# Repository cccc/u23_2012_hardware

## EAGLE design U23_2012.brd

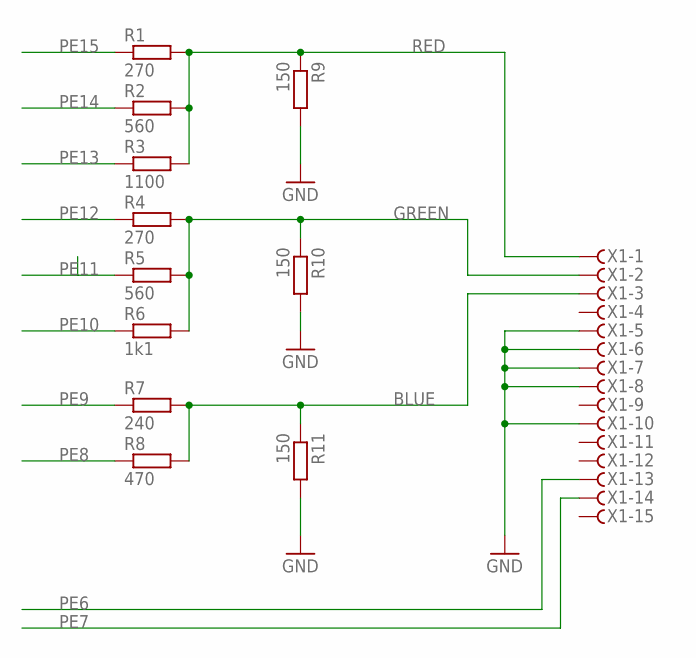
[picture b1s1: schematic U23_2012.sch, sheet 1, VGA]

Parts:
R1, R4: 270; 0207/10
R2, R5: 560; 0207/10
R3: 1100; 0207/10
R6: 1k1; 0207/10
R7: 240; 0207/10
R8: 470; 0207/10
R9, R10, R11: 150; 0207/10
X1: F15HDHS; HDF15H

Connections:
BLUE: R7.2, R8.2, R11.1, X1.3
GND: R9.2, R10.2, R11.2, X1.5, X1.6, X1.7, X1.8, X1.10; also elsewhere on the board
GREEN: R4.2, R5.2, R6.2, R10.1, X1.2
PE6: X1.13; also elsewhere on the board
PE7: X1.14; also elsewhere on the board
PE8: R8.1; also elsewhere on the board
PE9: R7.1; also elsewhere on the board
PE10: R6.1; also elsewhere on the board
PE11: R5.1; also elsewhere on the board
PE12: R4.1; also elsewhere on the board
PE13: R3.1; also elsewhere on the board
PE14: R2.1; also elsewhere on the board
PE15: R1.1; also elsewhere on the board
RED: R1.2, R2.2, R3.2, R9.1, X1.1

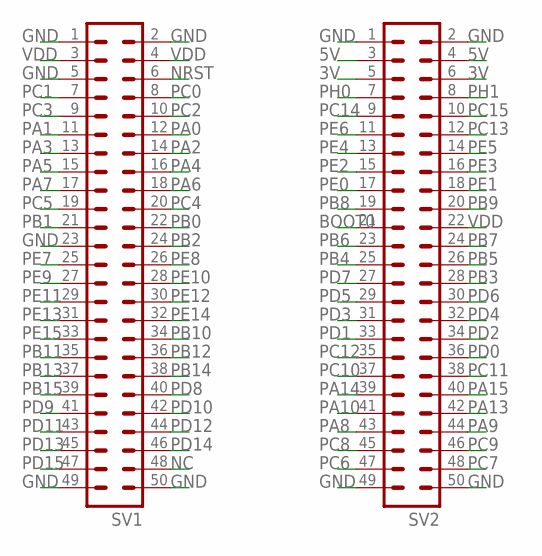
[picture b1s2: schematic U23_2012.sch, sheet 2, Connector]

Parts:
SV1, SV2: ML50

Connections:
3V: SV2.5, SV2.6; also elsewhere on the board
5V: SV2.3, SV2.4; also elsewhere on the board
BOOT0: SV2.21
GND: SV1.1, SV1.2, SV1.5, SV1.23, SV1.49, SV1.50, SV2.1, SV2.2, SV2.49, SV2.50; also elsewhere on the board
NC: SV1.48
NRST: SV1.6
PA0: SV1.12
PA1: SV1.11; also elsewhere on the board
PA2: SV1.14; also elsewhere on the board
PA3: SV1.13
PA4: SV1.16
PA5: SV1.15
PA6: SV1.18
PA7: SV1.17; also elsewhere on the board
PA8: SV2.43
PA9: SV2.44
PA10: SV2.41
PA13: SV2.42
PA14: SV2.39
PA15: SV2.40
PB0: SV1.22; also elsewhere on the board
PB1: SV1.21; also elsewhere on the board
PB2: SV1.24; also elsewhere on the board
PB3: SV2.28
PB4: SV2.25; also elsewhere on the board
PB5: SV2.26; also elsewhere on the board
PB6: SV2.23
PB7: SV2.24; also elsewhere on the board
PB8: SV2.19; also elsewhere on the board
PB9: SV2.20
PB10: SV1.34
PB11: SV1.35; also elsewhere on the board
PB12: SV1.36; also elsewhere on the board
PB13: SV1.37; also elsewhere on the board
PB14: SV1.38
PB15: SV1.39
PC0: SV1.8
PC1: SV1.7; also elsewhere on the board
PC2: SV1.10
PC3: SV1.9
PC4: SV1.20; also elsewhere on the board
PC5: SV1.19; also elsewhere on the board
PC6: SV2.47
PC7: SV2.48
PC8: SV2.45; also elsewhere on the board
PC9: SV2.46; also elsewhere on the board
PC10: SV2.37; also elsewhere on the board
PC11: SV2.38; also elsewhere on the board
PC12: SV2.35; also elsewhere on the board
PC13: SV2.12
PC14: SV2.9
PC15: SV2.10
PD0: SV2.36; also elsewhere on the board
PD1: SV2.33; also elsewhere on the board
PD2: SV2.34; also elsewhere on the board
PD3: SV2.31; also elsewhere on the board
PD4: SV2.32
PD5: SV2.29; also elsewhere on the board
PD6: SV2.30; also elsewhere on the board
PD7: SV2.27; also elsewhere on the board
PD8: SV1.40; also elsewhere on the board
PD9: SV1.41
PD10: SV1.42
PD11: SV1.43
PD12: SV1.44; also elsewhere on the board
PD13: SV1.45; also elsewhere on the board
PD14: SV1.46; also elsewhere on the board
PD15: SV1.47; also elsewhere on the board
PE0: SV2.17
PE1: SV2.18
PE2: SV2.15
PE3: SV2.16
PE4: SV2.13
PE5: SV2.14
PE6: SV2.11; also elsewhere on the board
PE7: SV1.25; also elsewhere on the board
PE8: SV1.26; also elsewhere on the board
PE9: SV1.27; also elsewhere on the board
PE10: SV1.28; also elsewhere on the board
PE11: SV1.29; also elsewhere on the board
PE12: SV1.30; also elsewhere on the board
PE13: SV1.31; also elsewhere on the board
PE14: SV1.32; also elsewhere on the board
PE15: SV1.33; also elsewhere on the board
PH0: SV2.7
PH1: SV2.8
VDD: SV1.3, SV1.4, SV2.22

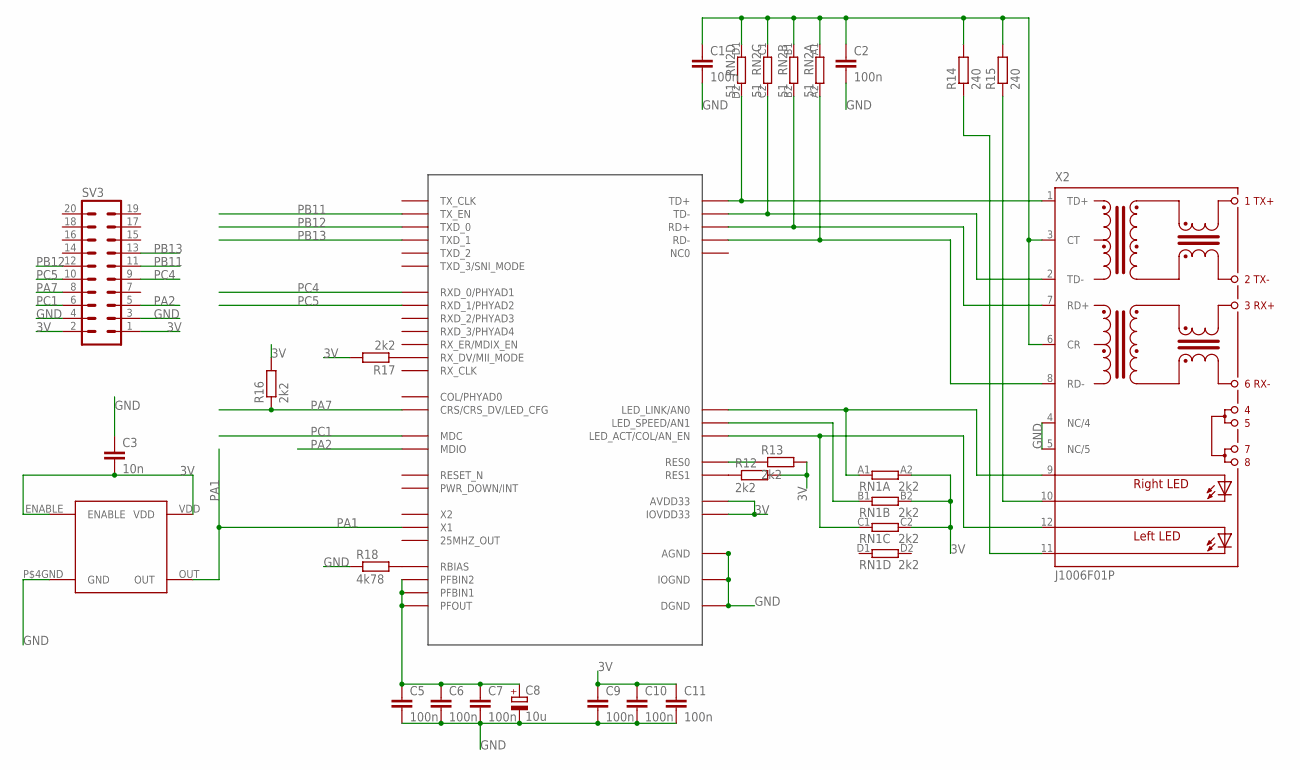
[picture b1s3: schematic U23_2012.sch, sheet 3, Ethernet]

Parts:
C1, C2, C5, C6, C7, C9, C10, C11: 100n; C0603
C3: 10n; C0603
C8: 10u; SMC_C
R12, R13, R16, R17: 2k2; R0603
R14, R15: 240; R0603
R18: 4k78; R0603
RN1: 2k2; CAR06ES
RN2: 51; CAR06ES
SV3: ML20L
U$1: DP83848CVV; LQFP-44
U$5: 50Mhz; FXO_HC73
X2: J1006F01P; J1

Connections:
3V: C3.2, C9.1, C10.1, C11.1, R12.2, R13.2, R16.2, R17.2, RN1.A2 (2), RN1.B2 (2), RN1.C2 (2), SV3.1, SV3.2, U$1.22 (AVDD33), U$1.32 (IOVDD33), U$1.48 (IOVDD33), U$5.ENABLE, U$5.VDD; also elsewhere on the board
GND: C1.2, C2.2, C3.1, C5.2, C6.2, C7.2, C8.-, C9.2, C10.2, C11.2, R18.1, SV3.3, SV3.4, U$1.15 (AGND), U$1.19 (AGND), U$1.35 (IOGND), U$1.36 (DGND), U$1.47 (IOGND), U$5.P$4GND (GND), X2.4 (NC/4), X2.5 (NC/5); also elsewhere on the board
unnamed: RN2.D2 (2), U$1.17 (TD+), X2.1 (TD+)
unnamed: RN2.C2 (2), U$1.16 (TD-), X2.2 (TD-)
unnamed: RN2.B2 (2), U$1.14 (RD+), X2.7 (RD+)
unnamed: RN2.A2 (2), U$1.13 (RD-), X2.8 (RD-)
unnamed: RN1.A1 (1), U$1.28 (LED_LINK/AN0), X2.9 (A-R)
unnamed: RN1.C1 (1), U$1.26 (LED_ACT/COL/AN_EN), X2.12 (A-L)
unnamed: RN1.B1 (1), U$1.27 (LED_SPEED/AN1)
unnamed: R12.1, U$1.21 (RES1)
unnamed: R13.1, U$1.20 (RES0)
unnamed: C1.1, C2.1, R14.2, R15.2, RN2.A1 (1), RN2.B1 (1), RN2.C1 (1), RN2.D1 (1), X2.3 (CT), X2.6 (CR)
unnamed: R17.1, U$1.39 (RX_DV/MII_MODE)
unnamed: R15.1, X2.10 (C-R)
unnamed: R14.1, X2.11 (C-L)
unnamed: R18.2, U$1.24 (RBIAS)
unnamed: C5.1, C6.1, C7.1, C8.+, U$1.18 (PFBIN1), U$1.23 (PFOUT), U$1.37 (PFBIN2)
PA1: U$1.34 (X1), U$5.OUT; also elsewhere on the board
PA2: SV3.5, U$1.30 (MDIO); also elsewhere on the board
PA7: R16.1, SV3.8, U$1.40 (CRS/CRS_DV/LED_CFG); also elsewhere on the board
PB11: SV3.11, U$1.2 (TX_EN); also elsewhere on the board
PB12: SV3.12, U$1.3 (TXD_0); also elsewhere on the board
PB13: SV3.13, U$1.4 (TXD_1); also elsewhere on the board
PC1: SV3.6, U$1.31 (MDC); also elsewhere on the board
PC4: SV3.9, U$1.43 (RXD_0/PHYAD1); also elsewhere on the board
PC5: SV3.10, U$1.44 (RXD_1/PHYAD2); also elsewhere on the board

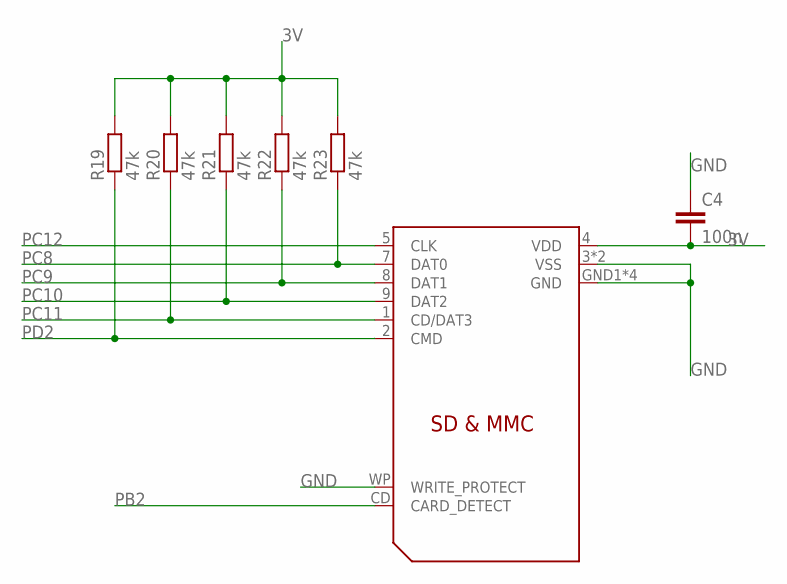
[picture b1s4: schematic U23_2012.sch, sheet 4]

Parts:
C4: 100n; C025-024X044
R19, R20, R21, R22, R23: 47k; 0207/10
U$2: SD-CARD; SD_CARD

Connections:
3V: C4.2, R19.2, R20.2, R21.2, R22.2, R23.2, U$2.4 (VDD); also elsewhere on the board
GND: C4.1, U$2.3 (VSS), U$2.6 (VSS), U$2.GND1 (GND), U$2.GND2 (GND), U$2.SHIELD1 (GND), U$2.SHIELD2 (GND), U$2.WP (WRITE_PROTECT); also elsewhere on the board
PB2: U$2.CD (CARD_DETECT); also elsewhere on the board
PC8: R23.1, U$2.7 (DAT0); also elsewhere on the board
PC9: R22.1, U$2.8 (DAT1); also elsewhere on the board
PC10: R21.1, U$2.9 (DAT2); also elsewhere on the board
PC11: R20.1, U$2.1 (CD/DAT3); also elsewhere on the board
PC12: U$2.5 (CLK); also elsewhere on the board
PD2: R19.1, U$2.2 (CMD); also elsewhere on the board

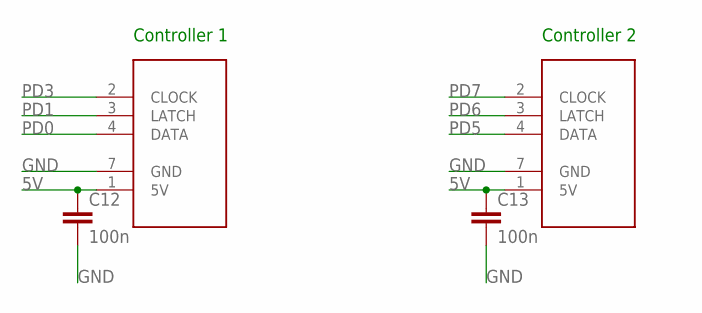
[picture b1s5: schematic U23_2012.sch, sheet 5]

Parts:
C12, C13: 100n; C025-024X044
U$3, U$4: SNES

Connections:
5V: C12.1, C13.1, U$3.1 (5V), U$4.1 (5V); also elsewhere on the board
GND: C12.2, C13.2, U$3.7 (GND), U$4.7 (GND); also elsewhere on the board
PD0: U$3.4 (DATA); also elsewhere on the board
PD1: U$3.3 (LATCH); also elsewhere on the board
PD3: U$3.2 (CLOCK); also elsewhere on the board
PD5: U$4.4 (DATA); also elsewhere on the board
PD6: U$4.3 (LATCH); also elsewhere on the board
PD7: U$4.2 (CLOCK); also elsewhere on the board

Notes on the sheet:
Controller 1
Controller 2

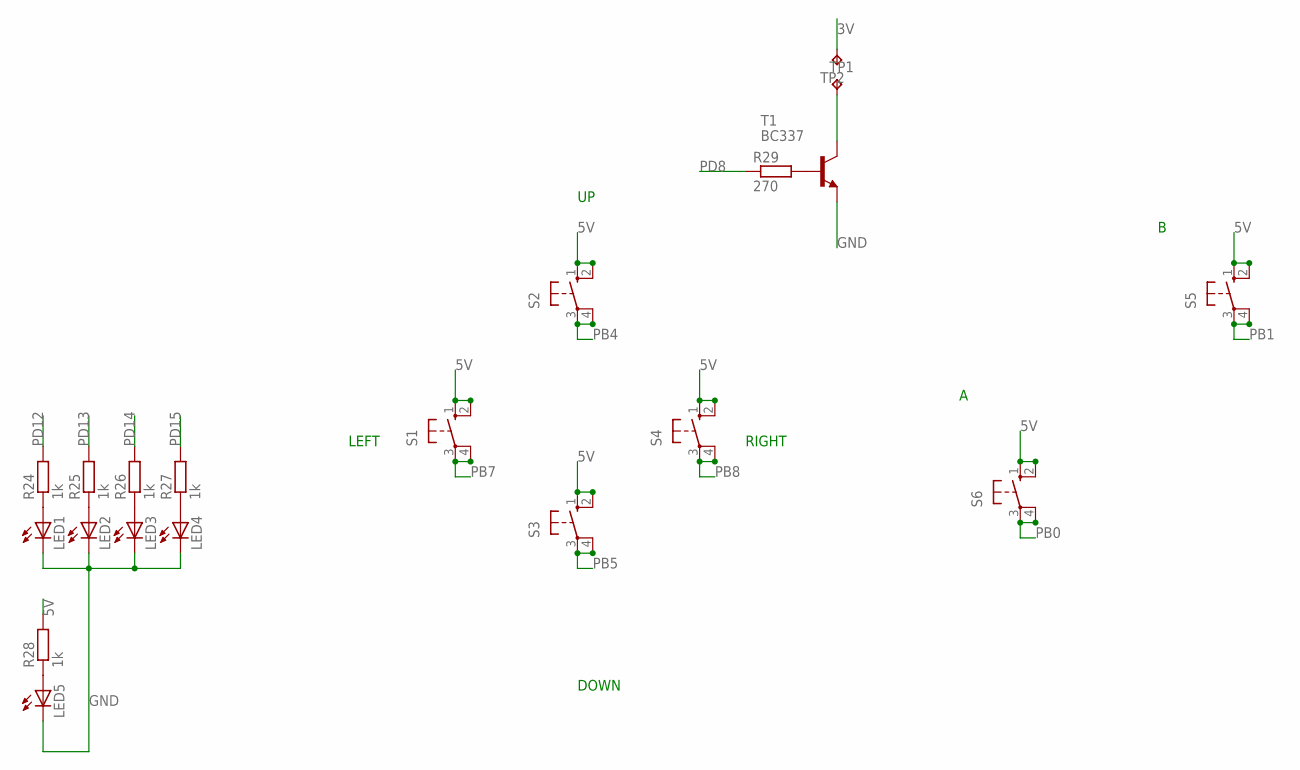
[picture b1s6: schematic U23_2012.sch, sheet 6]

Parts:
LED1, LED2, LED3, LED4, LED5: LED3MM
R24, R25, R26, R27, R28: 1k; 0207/10
R29: 270; 0207/10
S1, S2, S3, S4, S5, S6: 10-XX; B3F-10XX
T1: BC337; TO92
TP1, TP2: TPTP20SQ; TP20SQ

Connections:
3V: TP2.TP; also elsewhere on the board
5V: R28.2, S1.1 (S), S1.2 (S1), S2.1 (S), S2.2 (S1), S3.1 (S), S3.2 (S1), S4.1 (S), S4.2 (S1), S5.1 (S), S5.2 (S1), S6.1 (S), S6.2 (S1); also elsewhere on the board
GND: LED1.K (C), LED2.K (C), LED3.K (C), LED4.K (C), LED5.K (C), T1.1 (E); also elsewhere on the board
unnamed: LED1.A, R24.1
unnamed: LED2.A, R25.1
unnamed: LED3.A, R26.1
unnamed: LED4.A, R27.1
unnamed: LED5.A, R28.1
unnamed: R29.2, T1.2 (B)
unnamed: T1.3 (C), TP1.TP
PB0: S6.3, S6.4 (P1); also elsewhere on the board
PB1: S5.3, S5.4 (P1); also elsewhere on the board
PB4: S2.3, S2.4 (P1); also elsewhere on the board
PB5: S3.3, S3.4 (P1); also elsewhere on the board
PB7: S1.3, S1.4 (P1); also elsewhere on the board
PB8: S4.3, S4.4 (P1); also elsewhere on the board
PD8: R29.1; also elsewhere on the board
PD12: R24.2; also elsewhere on the board
PD13: R25.2; also elsewhere on the board
PD14: R26.2; also elsewhere on the board
PD15: R27.2; also elsewhere on the board

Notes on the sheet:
DOWN
RIGHT
LEFT

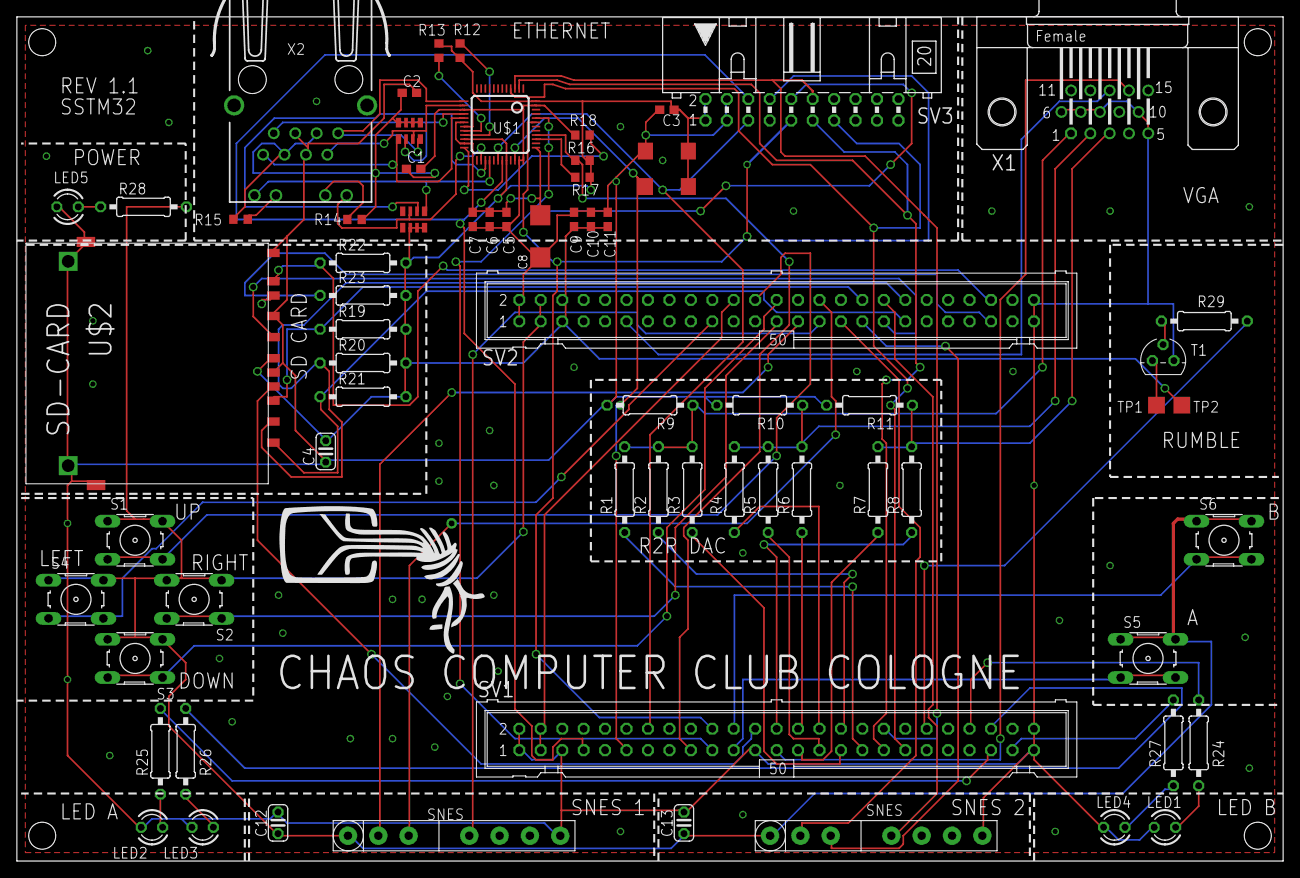
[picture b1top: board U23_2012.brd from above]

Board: 2 copper layers, 150.0 x 100.0 mm, 68 parts (0 on the bottom side), 72 nets.

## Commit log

2012-09-30 adds .gitignore
2012-09-30 adds misc page
2012-09-30 adds bom/partlist/pins
2012-09-30 removes pulldowns of buttons, due to internal pulldowns of MCU. Reexports netlist etc.
2012-09-30 adds missing base resistor to T1
2012-09-30 adds cheaper sources
2012-10-03 board rev 0.1
2012-10-03 fixes wrong routed signal
2012-10-03 adds drill files
2012-10-03 Adds PDF files
2012-10-12 adds connector to http://www.wvshare.com/product/DP83848-Ethernet-Board.htm Ethernet boards switches position of LED1 and LED5 adds silkscreen annotations etc removes pdf and drill files
2012-10-13 removes stupid mistake on ethernet jack
2012-10-13 fixes not connected vias. rev_1.1
2012-10-14 fixes wrong named ground plane
    committed to seed studio, rev_1.1_u23_final
    adds committed zip file
